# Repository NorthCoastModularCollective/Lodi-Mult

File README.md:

# Lodi Mult
## Overview
This is a 3hp passive 2x4 multiple for Eurorack that is intended to be stylish and easy for DIY. 

See [the WIKI for details](https://github.com/NorthCoastModularCollective/Mult/wiki), including BOM and build directions.

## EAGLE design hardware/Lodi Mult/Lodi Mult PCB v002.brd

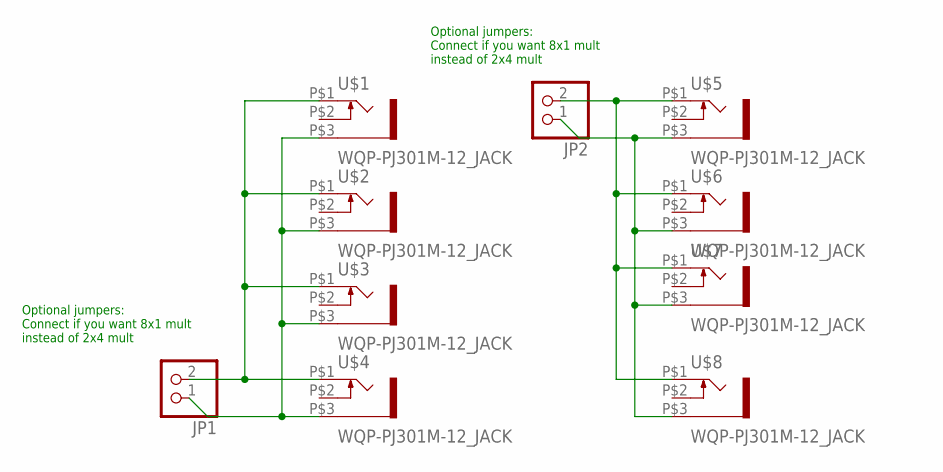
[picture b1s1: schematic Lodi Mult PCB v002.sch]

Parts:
JP1, JP2: PINHD-1X2; 1X02
U$1, U$2, U$3, U$4, U$5, U$6, U$7, U$8: WQP-PJ301M-12_JACK

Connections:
unnamed: JP1.2, U$1.P$1 (2), U$2.P$1 (2), U$3.P$1 (2), U$4.P$1 (2)
unnamed: JP1.1, U$1.P$3 (1), U$2.P$3 (1), U$3.P$3 (1), U$4.P$3 (1)
unnamed: JP2.2, U$5.P$1 (2), U$6.P$1 (2), U$7.P$1 (2), U$8.P$1 (2)
unnamed: JP2.1, U$5.P$3 (1), U$6.P$3 (1), U$7.P$3 (1), U$8.P$3 (1)

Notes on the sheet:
Optional jumpers: Connect if you want 8x1 mult instead of 2x4 mult

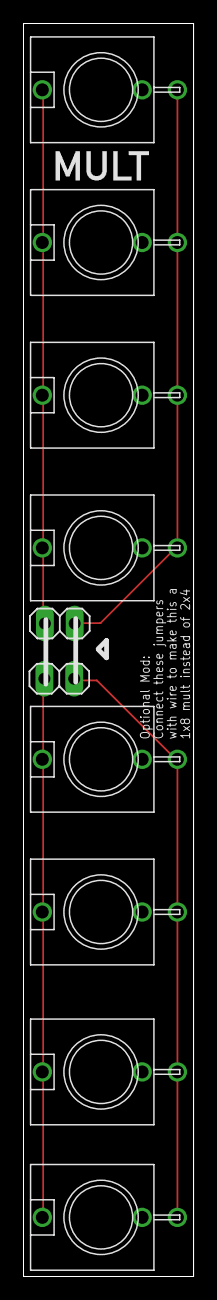
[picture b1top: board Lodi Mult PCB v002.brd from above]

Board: 2 copper layers, 14.5 x 106.7 mm, 10 parts (0 on the bottom side), 4 nets.

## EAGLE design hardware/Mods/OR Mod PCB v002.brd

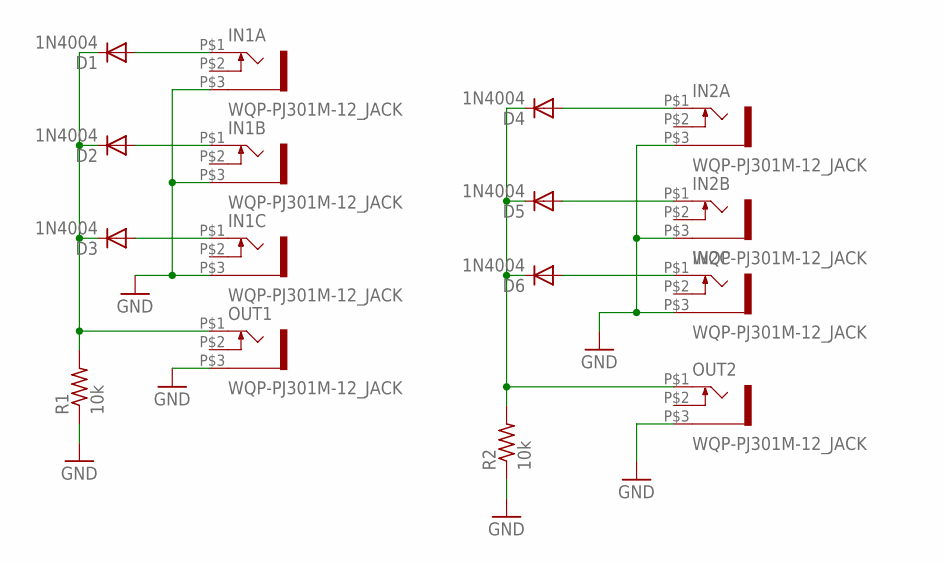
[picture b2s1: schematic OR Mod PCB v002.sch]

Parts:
D1, D2, D3, D4, D5, D6: 1N4004; DO41-10
IN1A, IN1B, IN1C, IN2A, IN2B, IN2C: WQP-PJ301M-12_JACK
OUT1, OUT2: WQP-PJ301M-12_JACK
R1, R2: 10k; 0204/7

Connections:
GND: IN1A.P$3 (1), IN1B.P$3 (1), IN1C.P$3 (1), IN2A.P$3 (1), IN2B.P$3 (1), IN2C.P$3 (1), OUT1.P$3 (1), OUT2.P$3 (1), R1.1, R2.1
unnamed: D1.C, D2.C, D3.C, OUT1.P$1 (2), R1.2
unnamed: D4.A, IN2A.P$1 (2)
unnamed: D6.A, IN2C.P$1 (2)
unnamed: D1.A, IN1A.P$1 (2)
unnamed: D2.A, IN1B.P$1 (2)
unnamed: D3.A, IN1C.P$1 (2)
unnamed: D5.A, IN2B.P$1 (2)
unnamed: D4.C, D5.C, D6.C, OUT2.P$1 (2), R2.2

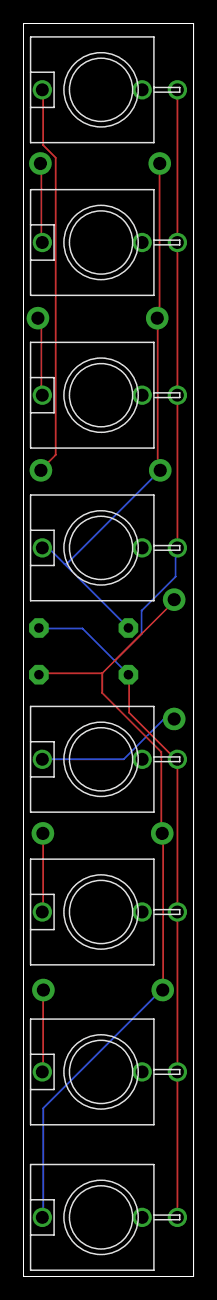
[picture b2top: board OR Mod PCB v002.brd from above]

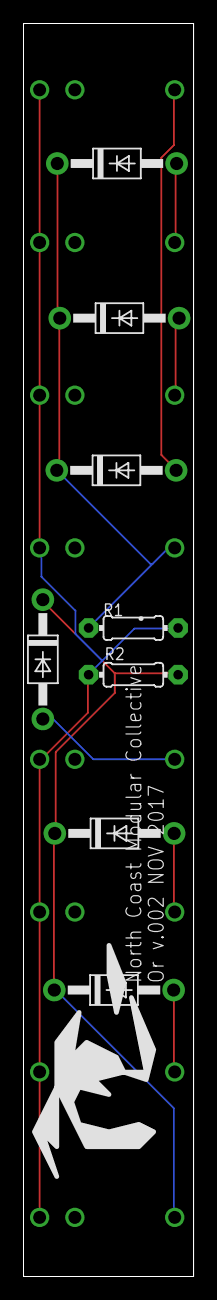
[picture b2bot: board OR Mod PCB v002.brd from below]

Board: 2 copper layers, 14.5 x 106.7 mm, 16 parts (8 on the bottom side), 9 nets.

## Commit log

2017-11-27 added image files
2017-11-27 added image
2017-11-27 version .002 boards and panel including OR mod
